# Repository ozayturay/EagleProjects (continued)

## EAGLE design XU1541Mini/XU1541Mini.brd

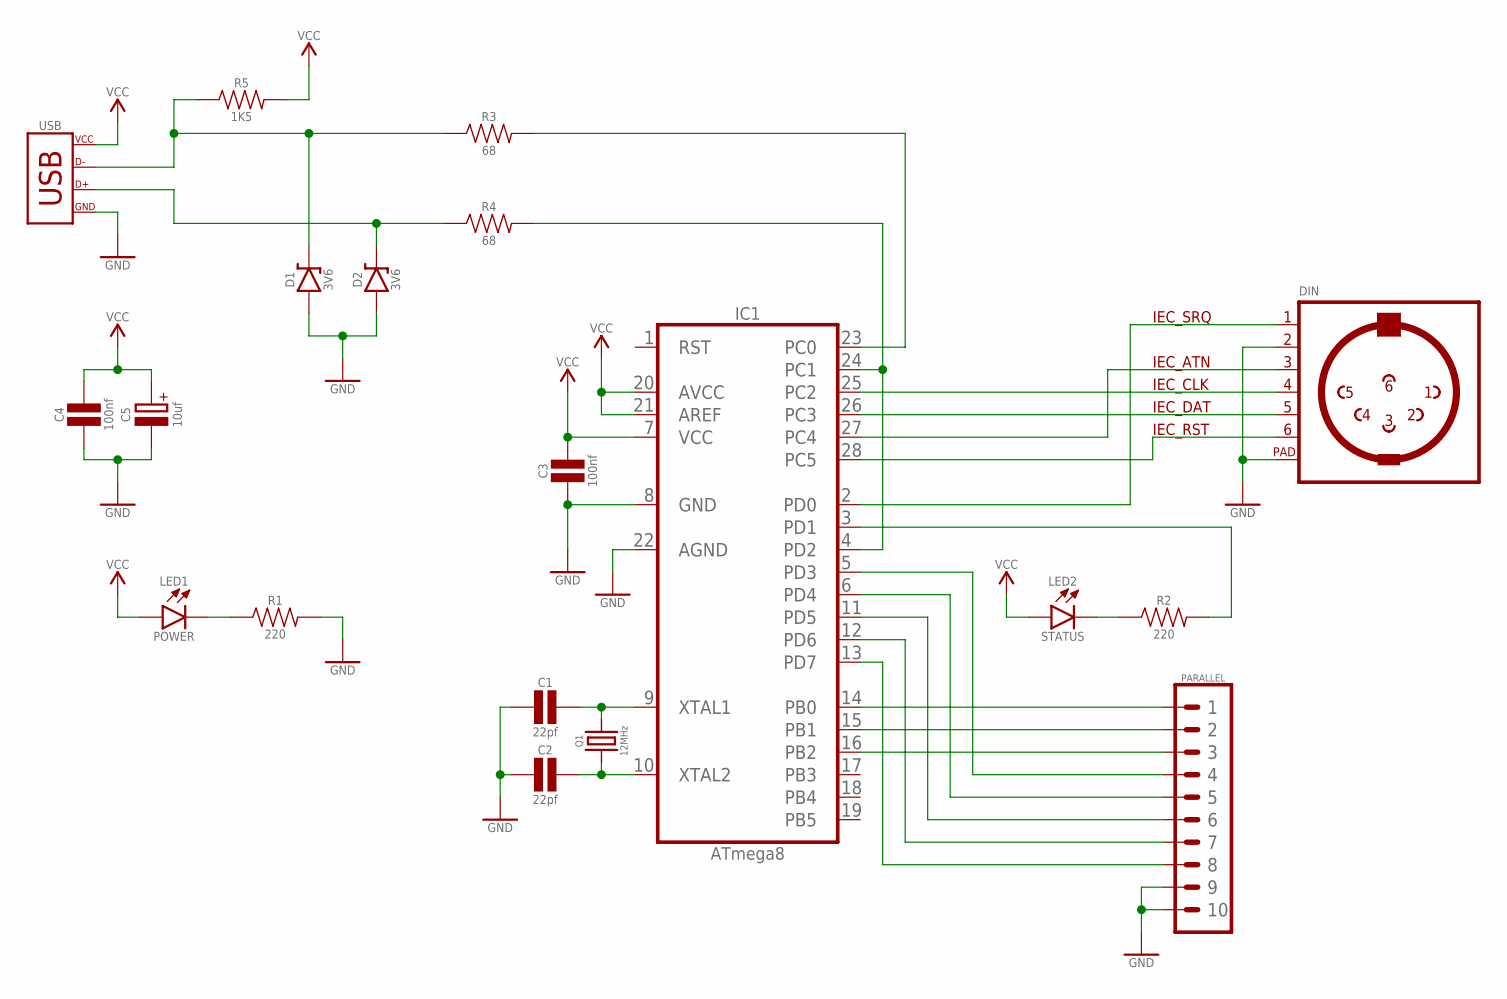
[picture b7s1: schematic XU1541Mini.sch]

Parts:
C1, C2: 22pf; CAPACITOR_CERAMIC_0.1
C3, C4: 100nf; CAPACITOR_CERAMIC_0.1
C5: 10uf; CAPACITOR_POLARIZED_0.1
D1, D2: 3V6; DIODE_ZENER_0.3
DIN: DIN6
IC1: ATmega8; DIP28
JP1: PARALLEL; HDR_2X05
LED1: POWER; LED_03MM
LED2: STATUS; LED_03MM
Q1: 12MHz; XTAL_HC49
R1, R2: 220; RESISTOR_THT_0.3
R3, R4: 68; RESISTOR_THT_0.3
R5: 1K5; RESISTOR_THT_0.3
USB: USB_TYPEB_THT

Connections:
3@1: IC1.3 (PD1), R2.2
3@2: LED2.CATHODE (C), R2.1
D+@1: D2.C (CATHODE), R4.1, USB.D+
D+@2: IC1.4 (PD2), IC1.24 (PC1), R4.2
D-@1: D1.C (CATHODE), R3.1, R5.1, USB.D-
D-@2: IC1.23 (PC0), R3.2
GND: C1.1, C2.1, C3.1, C4.1, C5.2 (-), D1.A (ANODE), D2.A (ANODE), DIN.2, DIN.PAD@1 (PAD), DIN.PAD@2 (PAD), IC1.8 (GND), IC1.22 (AGND), JP1.9, JP1.10, R1.2, USB.GND, USB.PAD@1 (GND), USB.PAD@2 (GND)
IEC_ATN: DIN.3, IC1.27 (PC4)
IEC_CLK: DIN.4, IC1.25 (PC2)
IEC_DAT: DIN.5, IC1.26 (PC3)
IEC_RST: DIN.6, IC1.28 (PC5)
IEC_SRQ: DIN.1, IC1.2 (PD0)
unnamed: IC1.14 (PB0), JP1.1
unnamed: IC1.15 (PB1), JP1.2
unnamed: IC1.16 (PB2), JP1.3
unnamed: IC1.5 (PD3), JP1.4
unnamed: IC1.6 (PD4), JP1.5
unnamed: IC1.11 (PD5), JP1.6
unnamed: IC1.12 (PD6), JP1.7
unnamed: IC1.13 (PD7), JP1.8
PWRLED: LED1.CATHODE (C), R1.1
VCC: C3.2, C4.2, C5.1 (+), IC1.7 (VCC), IC1.20 (AVCC), IC1.21 (AREF), LED1.ANODE (A), LED2.ANODE (A), R5.2, USB.VCC
XTAL1: C1.2, IC1.9 (XTAL1), Q1.2
XTAL2: C2.2, IC1.10 (XTAL2), Q1.1

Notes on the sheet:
IEC_SRQ
IEC_ATN
IEC_CLK
IEC_DAT
IEC_RST

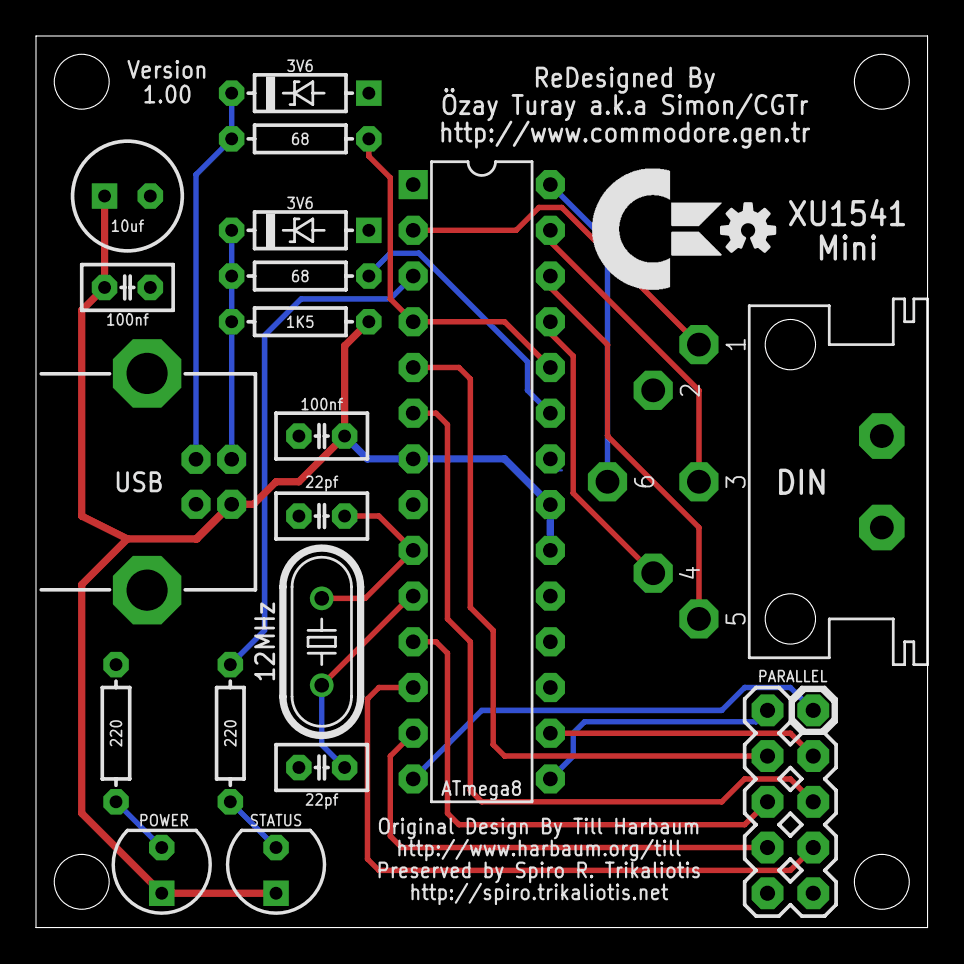
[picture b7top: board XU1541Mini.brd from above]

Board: 2 copper layers, 49.5 x 49.5 mm, 20 parts (0 on the bottom side), 24 nets.

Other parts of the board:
LOGO1: OSHW_LOGO_SMALL

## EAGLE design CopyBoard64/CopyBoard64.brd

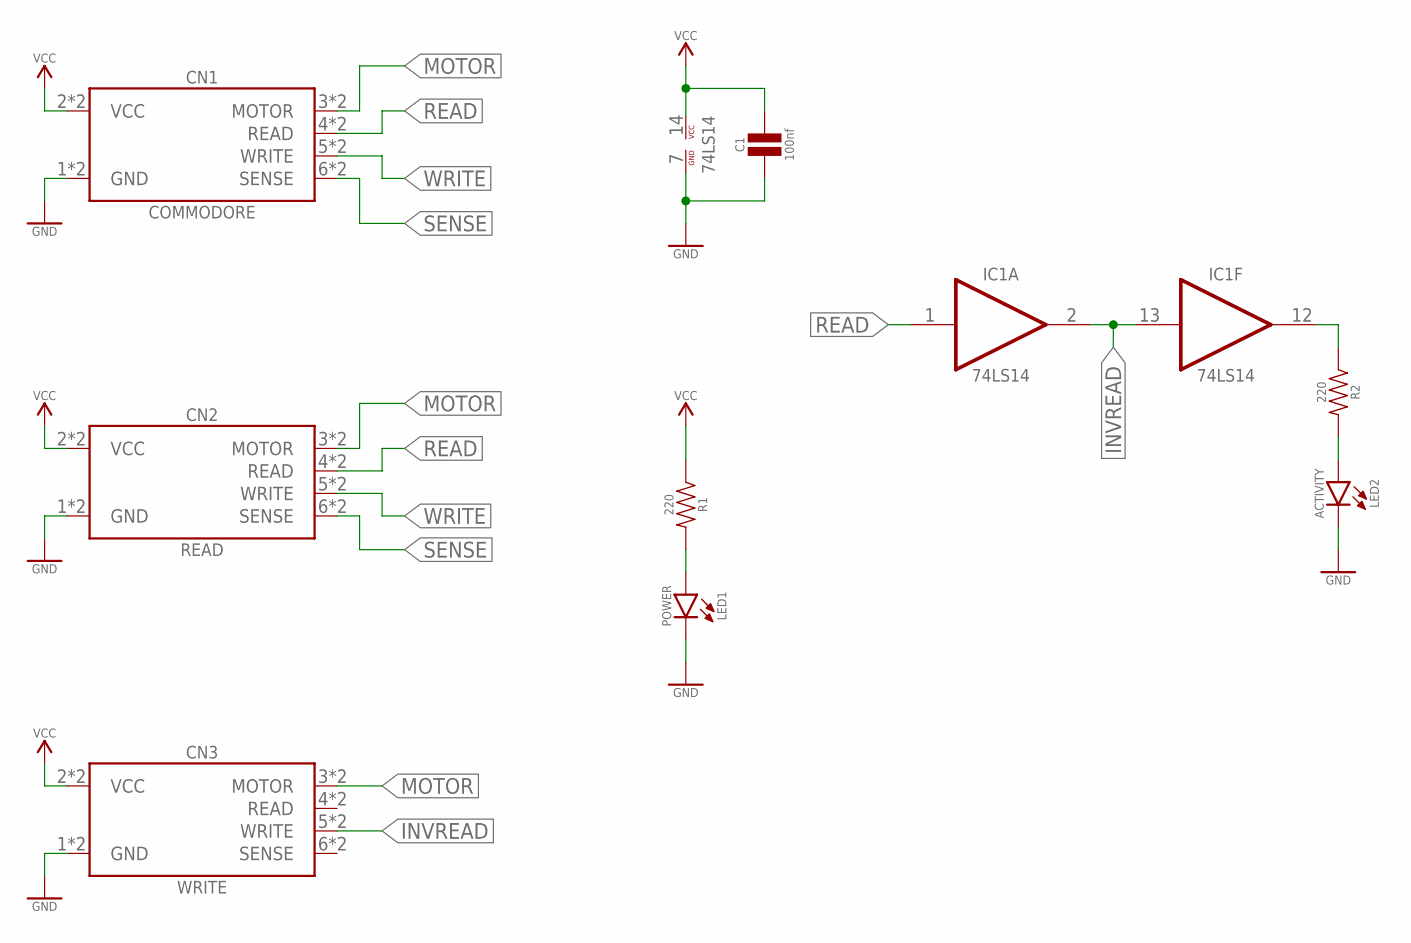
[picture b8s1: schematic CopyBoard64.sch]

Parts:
C1: 100nf; CAPACITOR_CERAMIC_0.2
CN1: COMMODORE; C64_DATASETTE
CN2: READ; C64_DATASETTE
CN3: WRITE; C64_DATASETTE
IC1: 74LS14; DIP14
LED1: POWER; LED_03MM
LED2: ACTIVITY; LED_03MM
R1, R2: 220; RESISTOR_0.3

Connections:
GND: C1.1, CN1.1 (GND), CN1.A (GND), CN2.1 (GND), CN2.A (GND), CN3.1 (GND), CN3.A (GND), IC1.7 (GND), LED1.CATHODE (C), LED2.CATHODE (C)
INVREAD: CN3.5 (WRITE), CN3.E (WRITE), IC1.2 (O), IC1.13 (I)
LEDA1: LED2.ANODE (A), R2.2
LEDA2: IC1.12 (O), R2.1
LEDP: LED1.ANODE (A), R1.2
MOTOR: CN1.3 (MOTOR), CN1.C (MOTOR), CN2.3 (MOTOR), CN2.C (MOTOR), CN3.3 (MOTOR), CN3.C (MOTOR)
READ: CN1.4 (READ), CN1.D (READ), CN2.4 (READ), CN2.D (READ), IC1.1 (I)
SENSE: CN1.6 (SENSE), CN1.F (SENSE), CN2.6 (SENSE), CN2.F (SENSE)
VCC: C1.2, CN1.2 (VCC), CN1.B (VCC), CN2.2 (VCC), CN2.B (VCC), CN3.2 (VCC), CN3.B (VCC), IC1.14 (VCC), R1.1
WRITE: CN1.5 (WRITE), CN1.E (WRITE), CN2.5 (WRITE), CN2.E (WRITE)

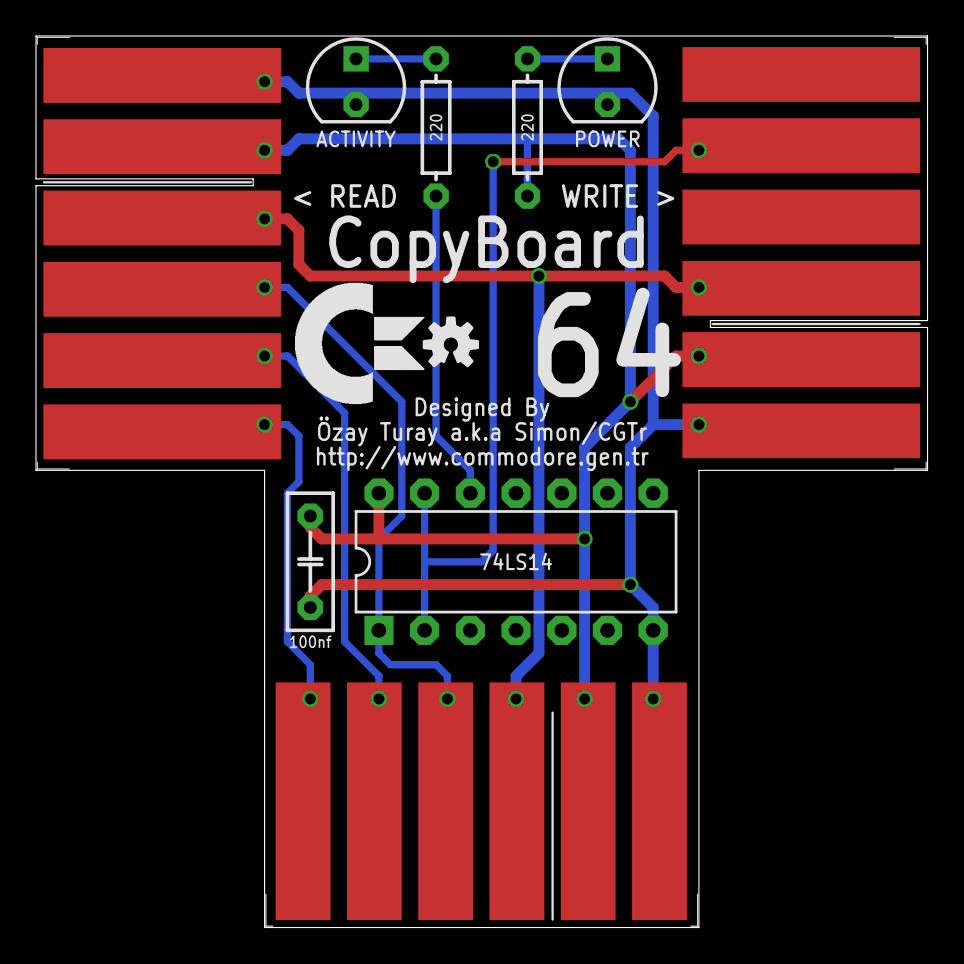
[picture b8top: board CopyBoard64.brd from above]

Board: 2 copper layers, 49.5 x 49.5 mm, 10 parts (1 on the bottom side), 10 nets.

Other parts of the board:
LOGO1: OSHW_LOGO_SMALL

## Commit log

2015-09-08 Added TapuinoMini project files
2015-09-08 Added KissCart64 project files
2015-09-08 Added XU1541Mini project files
2015-09-08 Added 27CXXX project files
2015-09-08 Added CopyBoard64 project files
2015-09-08 Added Eagle Libraries used for the projects
2015-09-09 Updated CopyBoard64 project files
2015-09-09 Updated KissCart64 project files
2015-09-09 Added Adafruit and SparkFun library zip files
2015-09-12 Updated TapuinoMini project files
2015-09-12 Updated project files and added missing preview images
2015-10-14 Added 27CXXXDouble panelized board and preview images
2015-11-25 Added IRQHack64 project files
2017-05-31 Added BBMiniPCB 5x5 and 5x10 versions project files
2018-02-22 Added RGBAmp project files, panelized gerber files and preview images
2018-05-11 Updated 27CXXX Design Files
2018-05-11 Update Libraries
2018-05-11 Added ADTWin project files, panelized gerber files and preview images
2018-05-11 Update IRQHack64 Design Files
2018-05-11 Update KissCart64 Design Files
2018-05-11 Added SD2IEC project files, panelized gerber files and preview images
2018-05-11 Updated TapuinoMini Design Files
2018-11-16 Backlink to CADLAB.io has been added.
2019-04-04 Added TapePower project files
2020-10-07 Added KissCart64 Gerber Files
